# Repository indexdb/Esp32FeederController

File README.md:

# Esp32FeederController & RGB WS2812 Controller

The project is forked from
https://github.com/atanisoft/Esp32FeederController

I added two RGB WS2812 Lights Controller

`M810 L{1|2} R{0-255} G{0-255} B{0-255}` to turn on light

`M811 L{1|2}` to turn off light

The Esp32FeederController project allows controlling of multiple 0816 Feeders
using four wire cables.

## Supported Feeders

At this time the following feeder designs should work:

* [Original 0816 Feeder](https://docs.mgrl.de/maschine:pickandplace:feeder:0816feeder).
* [0816 Lumen Feeder](https://github.com/SupaCoder/0816-Lumen-SMT-Feeder-Remix).
* [Max Feeder](https://github.com/CurlyTaleGamesLLC/MAXFeederShield).

The [Max Feeder](https://github.com/CurlyTaleGamesLLC/MAXFeederShield) is the preferred
version of the feeder design as it supports adding a QR Code to the feeder that can be
used for automatic part identification.

### Feeder modifications / Addons

* [Reel holder](https://www.thingiverse.com/thing:3810696)
* [Vertical tape puller](https://github.com/SebG3D/TapePuller/wiki)

## Non-automatic feeders

* [Lumen Push/Pull Feeder](https://github.com/GatCode/LumenPPF)

# Adding Esp32FeederController to OpenPnP

Adding Esp32FeederController to OpenPnP consists of three steps:

* Create [GcodeDriver](https://github.com/openpnp/openpnp/wiki/GcodeDriver).
* Create [Actuators](https://github.com/openpnp/openpnp/wiki/Setup-and-Calibration%3A-Actuators) for Feeder actions.
* Create [Feeders](https://github.com/openpnp/openpnp/wiki/Setup-and-Calibration%3A-Feeders). 

### Creating the Gcode Driver

Each Esp32FeederController PCB should have it's own [GcodeDriver](https://github.com/openpnp/openpnp/wiki/GcodeDriver).

Steps to add a new [GcodeDriver](https://github.com/openpnp/openpnp/wiki/GcodeDriver) for Esp32FeederController:

* Navigate to the `Machine Setup` tab
* Traverse the list to the `Drivers` section, select and expand it.
* Click the `+` (add) icon and select `GcodeDriver`.
* Select the newly created `GcodeDriver GcodeDriver` entry.
* Set the `Name` so it can be easily identified later.
* Set `Communications Type` to `tcp`.
* Scroll down to the `TCP` section.
* Set `IP Address` based on the reported IP address in the serial output.
* Set `Port` to `8989`.
* Click the `Apply` button to save the updates.
* In the `File` menu select `Save Configuration` to ensure settings are not lost when restarting OpenPnP.

### Creating Actuators

Each Esp32FeederController PCB requires two `Actuators`:

* Feeder Advancement
* Feeder Post Pick

The following steps should be executed for the two `Actuators`:

* Navigate to the `Machine Setup` tab
* Traverse the list to the `Actuators` section, select and expand it.
* Click the `+` (add) icon and select `ReferenceActuator`.
* Select the newly created `ReferenceActuator ReferenceActuator` entry.
* Set `Driver` to the Esp32FeederController driver created previously.
* Set the `Name` so it can be easily identified later.
* Set `Value Type` to `Double`.
* Click the `Apply` button to save the updates.
* In the `File` menu select `Save Configuration` to ensure settings are not lost when restarting OpenPnP.

After the two `Actuators` have been defined it is necessary to configure the
Gcode commands to send for actuation, use the following steps to configure this:

* Navigate to the `Machine Setup` tab
* Traverse the list to the `Drivers` section, select and expand it.
* Click the `GcodeDriver Esp32FeederController` (or whatever name was provided previously).
* Navigate to the `Gcode` tab.
* In `Head Mountable` drop down select `Default`.
  * In `Setting` select `COMMAND_CONFIRM_REGEX` and enter `^ok.*`, be sure to click `Apply` before moving further.
  * In `Setting` select `COMMAND_ERROR_REGEX` and enter `^error.*`, be sure to click `Apply` before moving further.
* In `Head Mountable` drop down select `Actuator: [No Head] Feeder Advancement`.
  * In `Setting` select `ACTUATE_DOUBLE_COMMAND` and enter `M610 N{IntegerValue}*`, be sure to click `Apply` before moving further.
* In `Head Mountable` drop down select `Actuator: [No Head] Feeder Post Pick`.
  * In `Setting` select `ACTUATE_DOUBLE_COMMAND` and enter `M611 N{IntegerValue}*`, be sure to click `Apply` before moving further.
* In the `File` menu select `Save Configuration` to ensure settings are not lost when restarting OpenPnP.

## Configuring Feeders in OpenPnP

There are two types of feeders that will work well with Esp32FeederController:

* [ReferenceAutoFeeder](https://github.com/openpnp/openpnp/wiki/ReferenceAutoFeeder)
* [ReferenceSlotAutoFeeder](https://github.com/openpnp/openpnp/wiki/ReferenceSlotAutoFeeder)

Both operate similarly using the `Actuators` defined above.

* Navigate to the `Feeders` tab
* Click the `+` (add) icon and select `ReferenceAutoFeeder` or `ReferenceSlotAutoFeeder`.
* Select the newly created `ReferenceAutoFeeder ReferenceAutoFeeder` or `ReferenceSlotAutoFeeder ReferenceSlotAutoFeeder` entry.
* Double click on the newly created row in the `Name` column and rename it for easier identification.
* Set `Feed Actuator` to `Feeder Advancement` (or whichever name you provide the `Actuator`)
* Set `Post Pick Actuator` to `Feeder Post Pick` (or whichever name you provide the `Actuator`)
* Set `Actuator Value` on both `Actuators` to the feeder number on the Esp32FeederController PCB minus one (zero indexed).
* Click the `Apply` button to save the updates.
* In the `File` menu select `Save Configuration` to ensure settings are not lost when restarting OpenPnP.

Use the `Test Feed` and `Test post pick` to confirm the feeder is responding correctly.

## Supported Gcode commands

The Esp32FeederController supports multiple Gcode commands, many of which are
not directly used by OpenPnP. Many of the commands are intended to be used with
substitution of values within `{ }` marks, anything within `[ ]` are optional
arguments.

### Feeder Movement (M610)

`M610 N{feeder} [D{distance}]`

* `{feeder}` is the Feeder to be moved forward.
* `{distance}` is the distance to move the feeder and is optional.

### Feeder Post Pick (M611)

`M611 N{feeder}`

* `{feeder}` is the Feeder to be moved as part of post-pick.

### Feeder Status (M612)

`M612 N{feeder}`

* `{feeder}` is the Feeder to retrieve status for.

### Feeder Configuration (M613)

`M613 N{feeder} [A{advance angle}] [B{half advance angle}] [C{retract angle}] [D{degrees}] [F{feed length}] [S{speed}] [U{settle time}] [V{min pulse}] [W{max pulse}] [Z{feedback enabled}]`

All parameters except `{feeder}` are optional.

* `{feeder}` is the Feeder to be configured.
* `{advance angle}` is the angle to move the servo to for full extension.
* `{half advance angle}` is the angle to move the servo to for half extension.
* `{retract angle}` is the angle to move the servo to for retraction.
* `{degrees}` is the maximum number of degrees to move at one time, set to zero to move immediately.
* `{feed length}` is the number of millimeters (pitch) to move the feeder forward when moving to the next part and must be a multiple of 2.
* `{speed}` is the interval at which to move the servo between two angles, used in conjunction with `{degrees}`.
* `{settle time}` is the number of milliseconds to delay between servo movements.
* `{min pulse}` is the minimum number of pulses to send the servo.
* `{max pulse}` is the maximum number of pulses to send the servo.
* `{feedback enabled}` is used to enable or disable feedback checking as part of movement, set to zero to disable or one to enable

### Enable Feeder (M614)

`M614 N{feeder}`

* `{feeder}` is the Feeder to enable.

### Disable Feeder (M615)

`M615 N{feeder}`

* `{feeder}` is the Feeder to disable.

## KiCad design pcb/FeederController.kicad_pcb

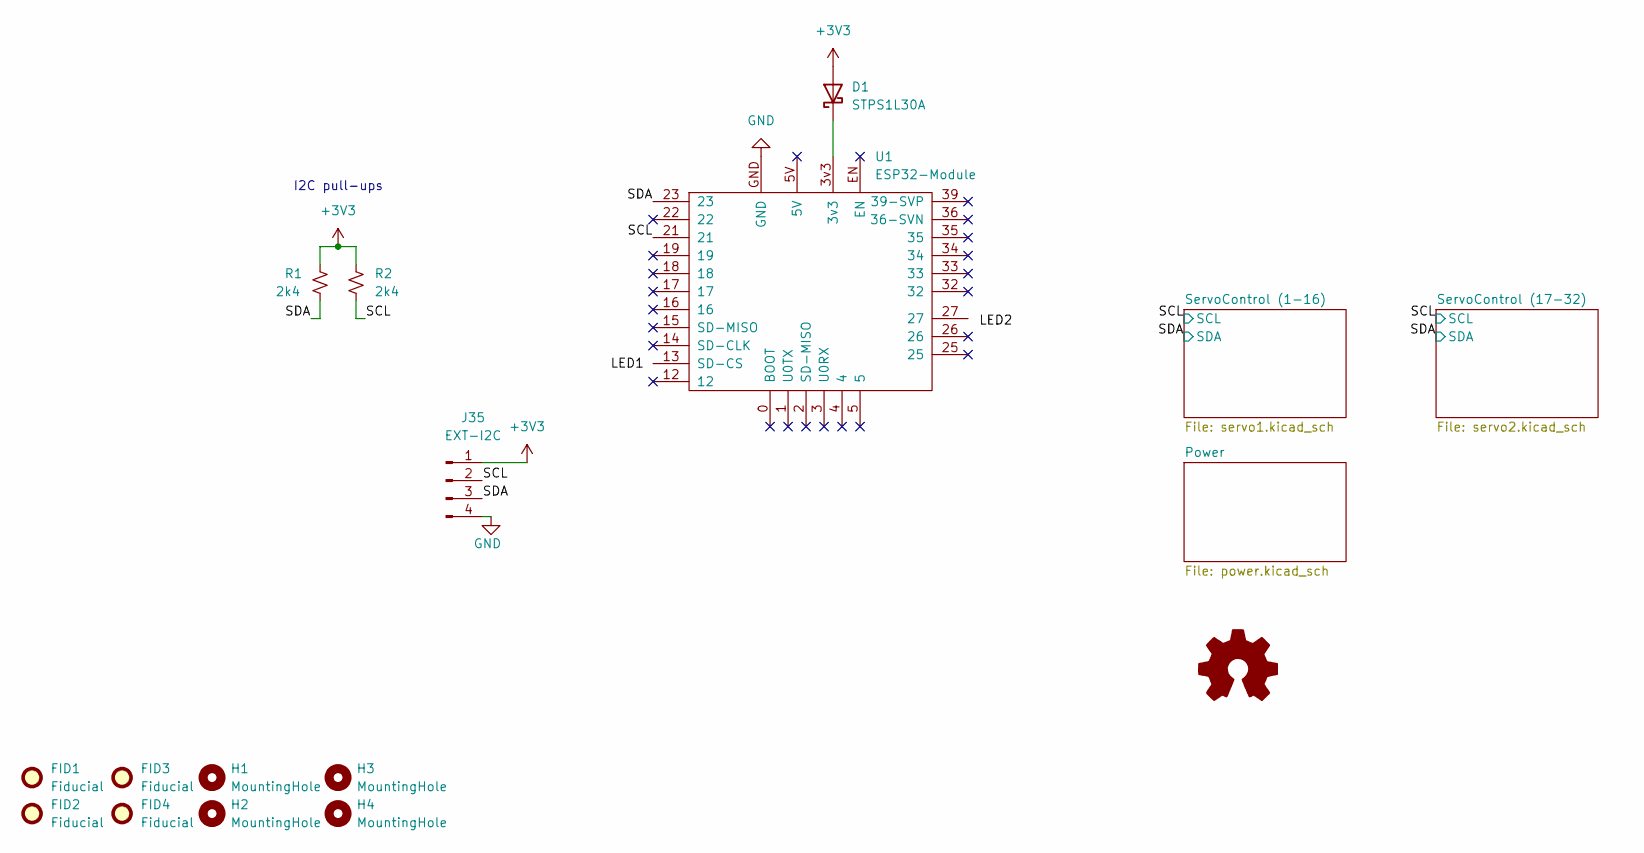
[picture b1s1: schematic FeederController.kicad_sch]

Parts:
D1: STPS1L30A; D_SMA_Handsoldering; Mouser 511-STPS1L30AFN
FID1, FID2, FID3, FID4: Fiducial; Fiducial_0.5mm_Mask1mm
H1, H2, H3, H4: MountingHole; MountingHole_3.2mm_M3_Pad
J35: EXT-I2C; PinHeader_1x04_P2.54mm_Vertical
R1, R2: 2k4; R_0603_1608Metric_Pad0.98x0.95mm_HandSolder
U1: ESP32-Module; TTGO-T1-DEVKIT-C

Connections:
/SCL: J35.2, R2.2, U1.21; also elsewhere on the board
/SDA: J35.3, R1.2, U1.23; also elsewhere on the board
GND: J35.4, U1.GND; also elsewhere on the board
unnamed: D1.1 (K), U1.3v3

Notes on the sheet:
I2C pull-ups

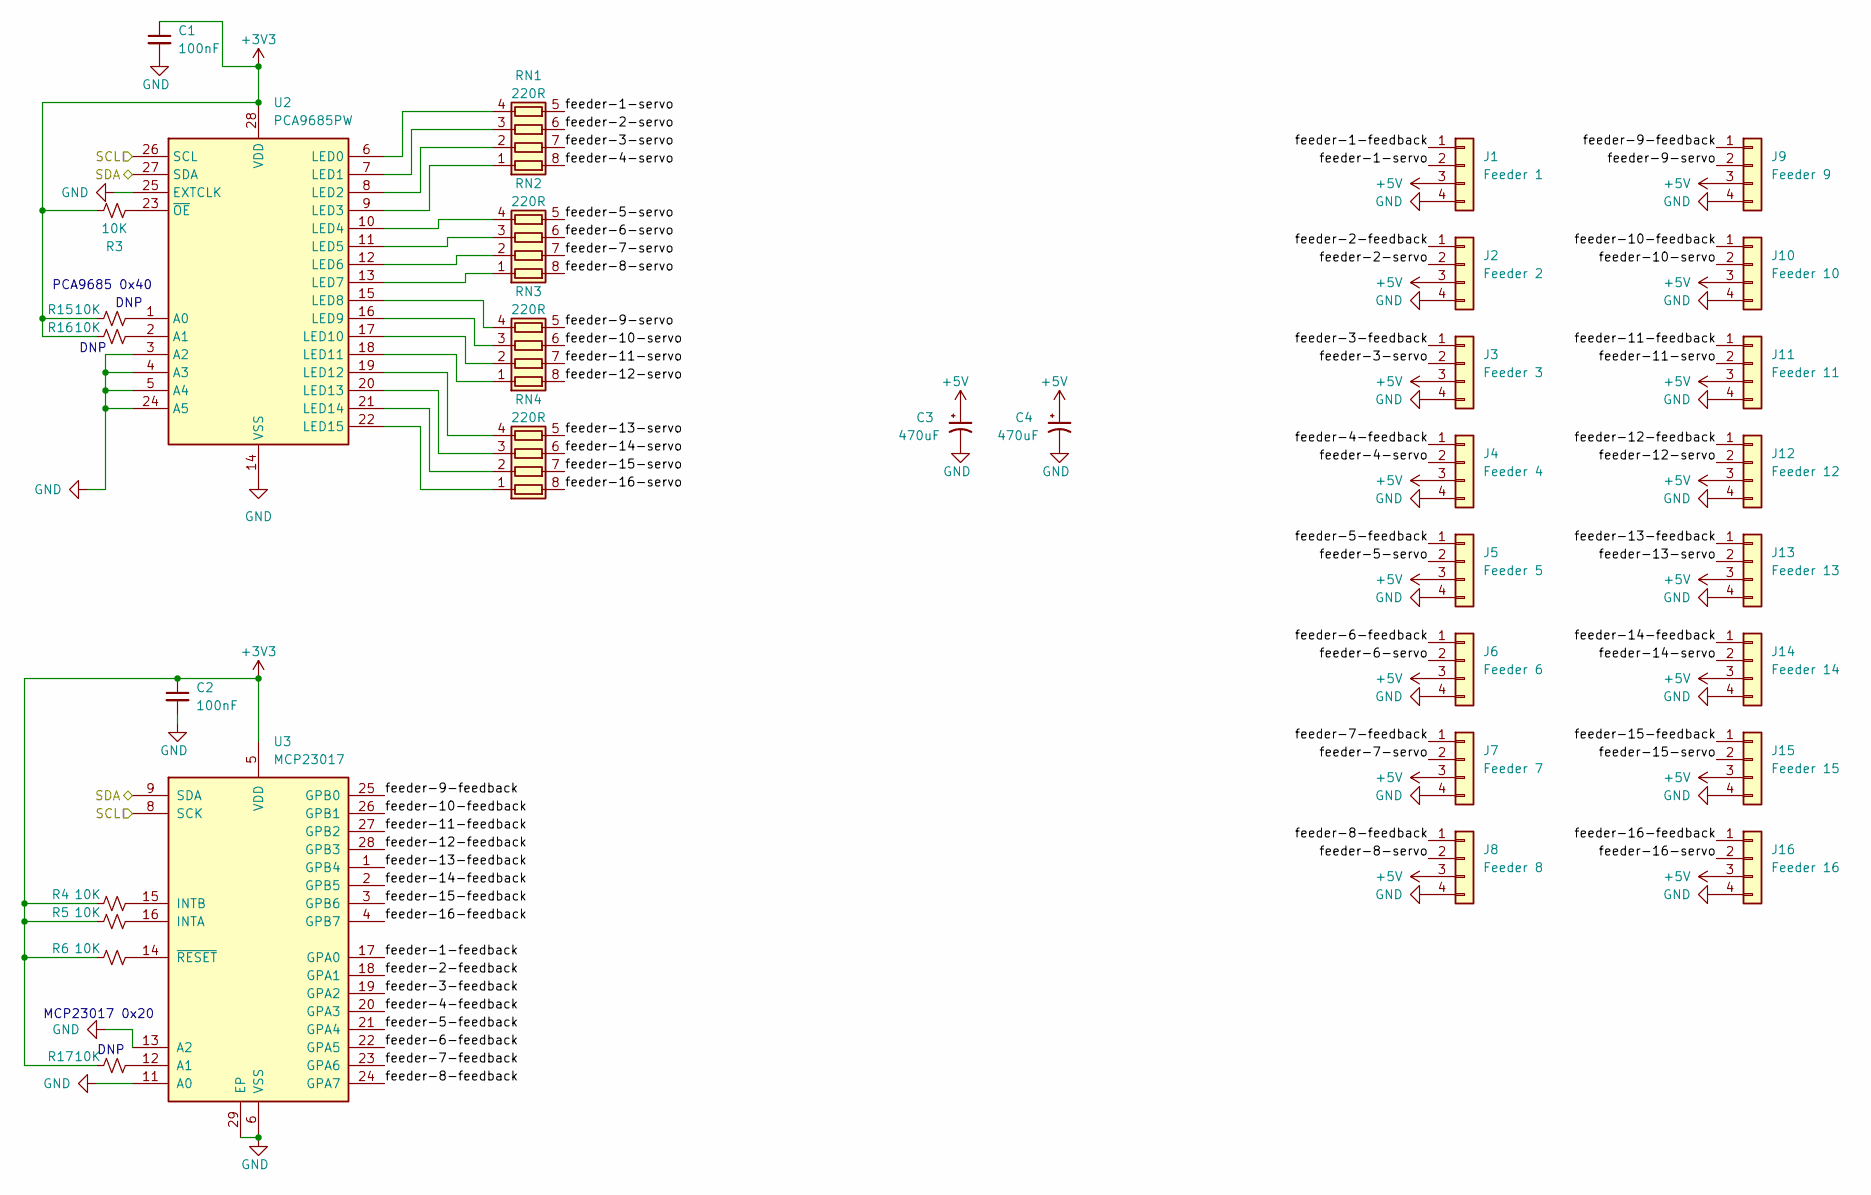
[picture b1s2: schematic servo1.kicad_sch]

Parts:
C1, C2: 100nF; C_0603_1608Metric_Pad1.08x0.95mm_HandSolder; Mouser 791-0603B822K250CT
C3, C4: 470uF; CP_Radial_D8.0mm_P5.00mm
J1: Feeder 1; PinHeader_1x04_P2.54mm_Vertical
J2: Feeder 2; PinHeader_1x04_P2.54mm_Vertical
J3: Feeder 3; PinHeader_1x04_P2.54mm_Vertical
J4: Feeder 4; PinHeader_1x04_P2.54mm_Vertical
J5: Feeder 5; PinHeader_1x04_P2.54mm_Vertical
J6: Feeder 6; PinHeader_1x04_P2.54mm_Vertical
J7: Feeder 7; PinHeader_1x04_P2.54mm_Vertical
J8: Feeder 8; PinHeader_1x04_P2.54mm_Vertical
J9: Feeder 9; PinHeader_1x04_P2.54mm_Vertical
J10: Feeder 10; PinHeader_1x04_P2.54mm_Vertical
J11: Feeder 11; PinHeader_1x04_P2.54mm_Vertical
J12: Feeder 12; PinHeader_1x04_P2.54mm_Vertical
J13: Feeder 13; PinHeader_1x04_P2.54mm_Vertical
J14: Feeder 14; PinHeader_1x04_P2.54mm_Vertical
J15: Feeder 15; PinHeader_1x04_P2.54mm_Vertical
J16: Feeder 16; PinHeader_1x04_P2.54mm_Vertical
R3, R4, R5, R6, R15, R16, R17: 10K; R_0603_1608Metric_Pad0.98x0.95mm_HandSolder; Mouser 279-CRGCQ0603F10K
RN1, RN2, RN3, RN4: 220R; R_Array_Concave_4x0402
U2: PCA9685PW; TSSOP-28_4.4x9.7mm_P0.65mm
U3: MCP23017; QFN-28-1EP_6x6mm_P0.65mm_EP4.25x4.25mm

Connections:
+5V: C3.1, C4.1, J1.3, J2.3, J3.3, J4.3, J5.3, J6.3, J7.3, J8.3, J9.3, J10.3, J11.3, J12.3, J13.3, J14.3, J15.3, J16.3; also elsewhere on the board
/SCL: U2.26 (SCL), U3.8 (SCK); also elsewhere on the board
/SDA: U2.27 (SDA), U3.9 (SDA); also elsewhere on the board
/ServoControl (1-16)/feeder-1-feedback: J1.1, U3.17 (GPA0)
/ServoControl (1-16)/feeder-1-servo: J1.2, RN1.5 (R4.2)
/ServoControl (1-16)/feeder-2-feedback: J2.1, U3.18 (GPA1)
/ServoControl (1-16)/feeder-2-servo: J2.2, RN1.6 (R3.2)
/ServoControl (1-16)/feeder-3-feedback: J3.1, U3.19 (GPA2)
/ServoControl (1-16)/feeder-3-servo: J3.2, RN1.7 (R2.2)
/ServoControl (1-16)/feeder-4-feedback: J4.1, U3.20 (GPA3)
/ServoControl (1-16)/feeder-4-servo: J4.2, RN1.8 (R1.2)
/ServoControl (1-16)/feeder-5-feedback: J5.1, U3.21 (GPA4)
/ServoControl (1-16)/feeder-5-servo: J5.2, RN2.5 (R4.2)
/ServoControl (1-16)/feeder-6-feedback: J6.1, U3.22 (GPA5)
/ServoControl (1-16)/feeder-6-servo: J6.2, RN2.6 (R3.2)
/ServoControl (1-16)/feeder-7-feedback: J7.1, U3.23 (GPA6)
/ServoControl (1-16)/feeder-7-servo: J7.2, RN2.7 (R2.2)
/ServoControl (1-16)/feeder-8-feedback: J8.1, U3.24 (GPA7)
/ServoControl (1-16)/feeder-8-servo: J8.2, RN2.8 (R1.2)
/ServoControl (1-16)/feeder-9-feedback: J9.1, U3.25 (GPB0)
/ServoControl (1-16)/feeder-9-servo: J9.2, RN3.5 (R4.2)
/ServoControl (1-16)/feeder-10-feedback: J10.1, U3.26 (GPB1)
/ServoControl (1-16)/feeder-10-servo: J10.2, RN3.6 (R3.2)
/ServoControl (1-16)/feeder-11-feedback: J11.1, U3.27 (GPB2)
/ServoControl (1-16)/feeder-11-servo: J11.2, RN3.7 (R2.2)
/ServoControl (1-16)/feeder-12-feedback: J12.1, U3.28 (GPB3)
/ServoControl (1-16)/feeder-12-servo: J12.2, RN3.8 (R1.2)
/ServoControl (1-16)/feeder-13-feedback: J13.1, U3.1 (GPB4)
/ServoControl (1-16)/feeder-13-servo: J13.2, RN4.5 (R4.2)
/ServoControl (1-16)/feeder-14-feedback: J14.1, U3.2 (GPB5)
/ServoControl (1-16)/feeder-14-servo: J14.2, RN4.6 (R3.2)
/ServoControl (1-16)/feeder-15-feedback: J15.1, U3.3 (GPB6)
/ServoControl (1-16)/feeder-15-servo: J15.2, RN4.7 (R2.2)
/ServoControl (1-16)/feeder-16-feedback: J16.1, U3.4 (GPB7)
/ServoControl (1-16)/feeder-16-servo: J16.2, RN4.8 (R1.2)
GND: C1.2, C2.2, C3.2, C4.2, J1.4, J2.4, J3.4, J4.4, J5.4, J6.4, J7.4, J8.4, J9.4, J10.4, J11.4, J12.4, J13.4, J14.4, J15.4, J16.4, R3.2, U2.3 (A2), U2.4 (A3), U2.5 (A4), U2.14 (VSS), U2.23 (~OE), U2.24 (A5), U2.25 (EXTCLK), U3.6 (VSS), U3.11 (A0), U3.13 (A2), U3.29 (EP); also elsewhere on the board
unnamed: R4.2, U3.15 (INTB)
unnamed: R5.2, U3.16 (INTA)
unnamed: R6.2, U3.14 (~RESET)
unnamed: RN1.1 (R1.1), U2.9 (LED3)
unnamed: RN1.2 (R2.1), U2.8 (LED2)
unnamed: RN1.3 (R3.1), U2.7 (LED1)
unnamed: RN1.4 (R4.1), U2.6 (LED0)
unnamed: RN2.1 (R1.1), U2.13 (LED7)
unnamed: RN2.2 (R2.1), U2.12 (LED6)
unnamed: RN2.3 (R3.1), U2.11 (LED5)
unnamed: RN2.4 (R4.1), U2.10 (LED4)
unnamed: RN3.1 (R1.1), U2.18 (LED11)
unnamed: RN3.2 (R2.1), U2.17 (LED10)
unnamed: RN3.3 (R3.1), U2.16 (LED9)
unnamed: RN3.4 (R4.1), U2.15 (LED8)
unnamed: RN4.1 (R1.1), U2.22 (LED15)
unnamed: RN4.2 (R2.1), U2.21 (LED14)
unnamed: RN4.3 (R3.1), U2.20 (LED13)
unnamed: RN4.4 (R4.1), U2.19 (LED12)
unnamed: R15.2, U2.1 (A0)
unnamed: R16.2, U2.2 (A1)
unnamed: R17.2, U3.12 (A1)

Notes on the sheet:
MCP23017 0x20
PCA9685 0x40
DNP

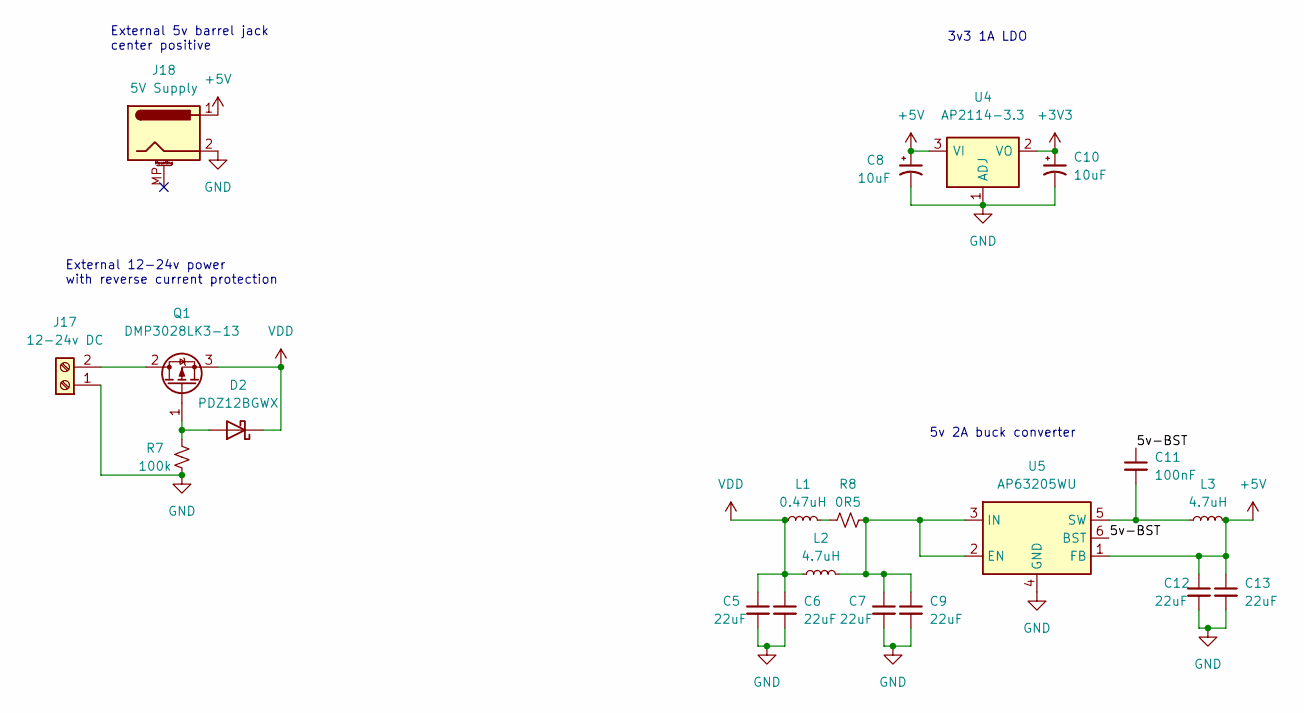
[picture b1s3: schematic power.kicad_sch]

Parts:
C5, C6, C9, C12, C13: 22uF; C_0603_1608Metric_Pad1.08x0.95mm_HandSolder; Mouser 810-C1608X5R0J226M
C7: 22uF; C_0603_1608Metric_Pad1.08x0.95mm_HandSolder; Mouser 810-C1608X5R0J226
C8, C10: 10uF; CP_Elec_5x5.3; Mouser 710-865230542002
C11: 100nF; C_0603_1608Metric_Pad1.08x0.95mm_HandSolder; Mouser 603-CC603KPX7R9BB104
D2: PDZ12BGWX; D_SOD-123; Mouser 771-PDZ12BGWX
J17: 12-24v DC; TerminalBlock_Phoenix_MKDS-1,5-2-5.08_1x02_P5.08mm_Horizont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; Mouser 649-220316-H021B01LF
J18: 5V Supply; BarrelJack_Horizontal
L1: 0.47uH; L_0603_1608Metric_Pad1.05x0.95mm_HandSolder; Mouser 810-MLZ1608DR47DT000
L2, L3: 4.7uH; L_Taiyo-Yuden_NR-40xx_HandSoldering; Mouser 963-NRS4018T4R7MDGJ
Q1: DMP3028LK3-13; TO-252-2; Mouser 621-DMP3028LK3-13
R7: 100k; R_1206_3216Metric_Pad1.30x1.75mm_HandSolder; Mouser 71-CRCW1206100KFKEAC
R8: 0R5; R_0805_2012Metric_Pad1.20x1.40mm_HandSolder; Mouser 756-LRCS0805-R50FT5
U4: AP2114-3.3; SOT-223-3_TabPin2; Mouser 621-AP2114H-3.3TRG1
U5: AP63205WU; TSOT-23-6; Mouser 621-AP63205WU-7

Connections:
+5V: C8.1, C12.1, C13.1, J18.1, L3.2, U4.3 (VI), U5.1 (FB); also elsewhere on the board
/Power/5v-BST: C11.1, U5.6 (BST)
GND: C5.2, C6.2, C7.2, C8.2, C9.2, C10.2, C12.2, C13.2, J17.1, J18.2, R7.1, U4.1 (ADJ), U5.4 (GND); also elsewhere on the board
unnamed: C7.1, C9.1, L2.2, R8.2, U5.2 (EN), U5.3 (IN)
unnamed: C11.2, L3.1, U5.5 (SW)
unnamed: D2.2 (A), Q1.1 (G), R7.2
unnamed: J17.2, Q1.2 (D)
unnamed: L1.2, R8.1
VDD: C5.1, C6.1, D2.1 (K), L1.1, L2.1, Q1.3 (S)

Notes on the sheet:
5v 2A buck converter
External 12-24v power with reverse current protection
3v3 1A LDO
External 5v barrel jack center positive

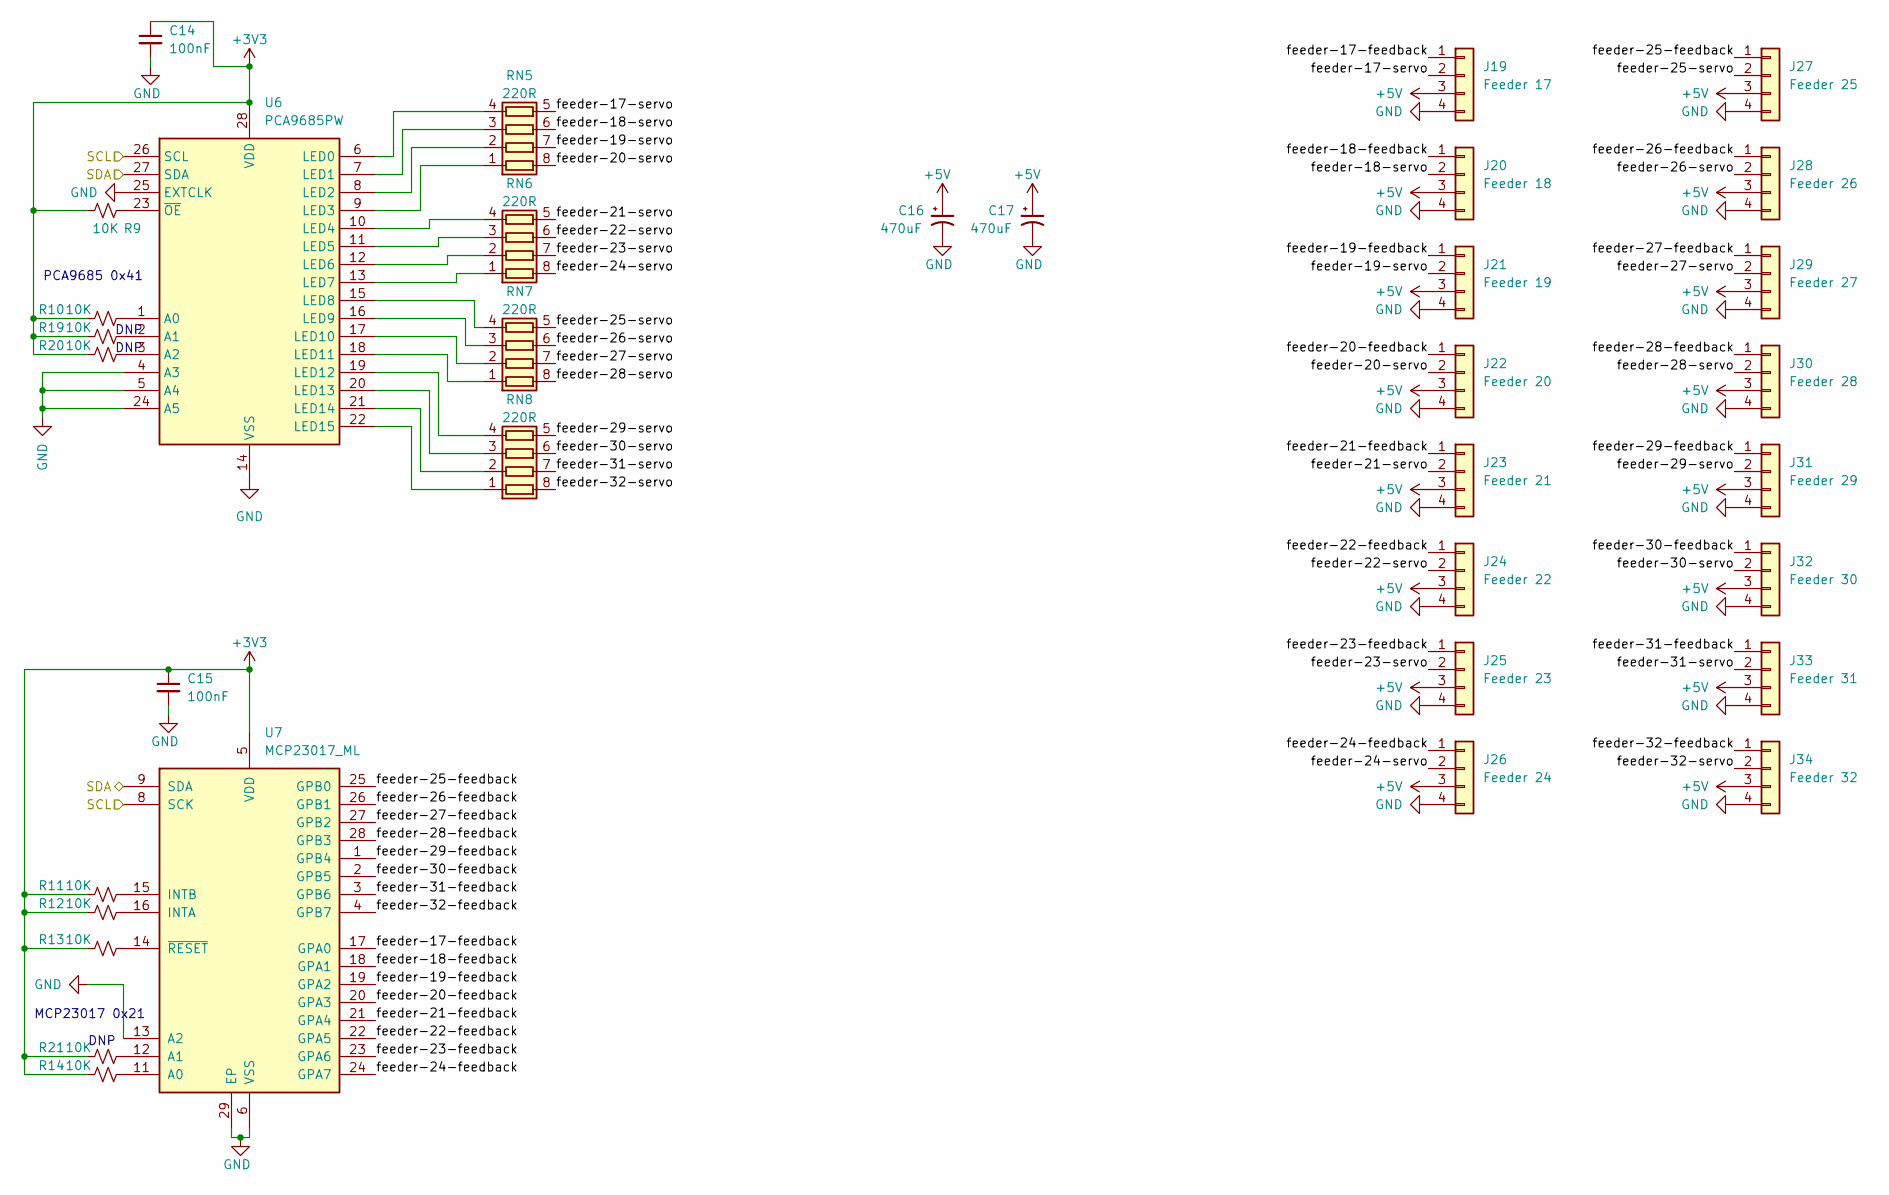
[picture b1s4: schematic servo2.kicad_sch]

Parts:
C14: 100nF; C_0603_1608Metric_Pad1.08x0.95mm_HandSolder
C15: 100nF; C_0603_1608Metric_Pad1.08x0.95mm_HandSolder; Mouser 791-0603B822K250CT
C16, C17: 470uF; CP_Radial_D8.0mm_P5.00mm
J19: Feeder 17; PinHeader_1x04_P2.54mm_Vertical
J20: Feeder 18; PinHeader_1x04_P2.54mm_Vertical
J21: Feeder 19; PinHeader_1x04_P2.54mm_Vertical
J22: Feeder 20; PinHeader_1x04_P2.54mm_Vertical
J23: Feeder 21; PinHeader_1x04_P2.54mm_Vertical
J24: Feeder 22; PinHeader_1x04_P2.54mm_Vertical
J25: Feeder 23; PinHeader_1x04_P2.54mm_Vertical
J26: Feeder 24; PinHeader_1x04_P2.54mm_Vertical
J27: Feeder 25; PinHeader_1x04_P2.54mm_Vertical
J28: Feeder 26; PinHeader_1x04_P2.54mm_Vertical
J29: Feeder 27; PinHeader_1x04_P2.54mm_Vertical
J30: Feeder 28; PinHeader_1x04_P2.54mm_Vertical
J31: Feeder 29; PinHeader_1x04_P2.54mm_Vertical
J32: Feeder 30; PinHeader_1x04_P2.54mm_Vertical
J33: Feeder 31; PinHeader_1x04_P2.54mm_Vertical
J34: Feeder 32; PinHeader_1x04_P2.54mm_Vertical
R9, R10, R11, R12, R13, R14, R19, R20, R21: 10K; R_0603_1608Metric_Pad0.98x0.95mm_HandSolder; Mouser 279-CRGCQ0603F10K
RN5, RN6, RN7, RN8: 220R; R_Array_Concave_4x0402
U6: PCA9685PW; TSSOP-28_4.4x9.7mm_P0.65mm
U7: MCP23017_ML; QFN-28-1EP_6x6mm_P0.65mm_EP4.25x4.25mm

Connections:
+5V: C16.1, C17.1, J19.3, J20.3, J21.3, J22.3, J23.3, J24.3, J25.3, J26.3, J27.3, J28.3, J29.3, J30.3, J31.3, J32.3, J33.3, J34.3; also elsewhere on the board
/SCL: U6.26 (SCL), U7.8 (SCK); also elsewhere on the board
/SDA: U6.27 (SDA), U7.9 (SDA); also elsewhere on the board
/ServoControl (17-32)/feeder-17-servo: J19.2, RN5.5 (R4.2); also elsewhere on the board
/ServoControl (17-32)/feeder-18-feedback: J20.1, U7.18 (GPA1)
/ServoControl (17-32)/feeder-18-servo: J20.2, RN5.6 (R3.2)
/ServoControl (17-32)/feeder-19-feedback: J21.1, U7.19 (GPA2)
/ServoControl (17-32)/feeder-19-servo: J21.2, RN5.7 (R2.2)
/ServoControl (17-32)/feeder-20-feedback: J22.1, U7.20 (GPA3)
/ServoControl (17-32)/feeder-20-servo: J22.2, RN5.8 (R1.2)
/ServoControl (17-32)/feeder-21-feedback: J23.1, U7.21 (GPA4)
/ServoControl (17-32)/feeder-21-servo: J23.2, RN6.5 (R4.2)
/ServoControl (17-32)/feeder-22-feedback: J24.1, U7.22 (GPA5)
/ServoControl (17-32)/feeder-22-servo: J24.2, RN6.6 (R3.2)
/ServoControl (17-32)/feeder-23-feedback: J25.1, U7.23 (GPA6)
/ServoControl (17-32)/feeder-23-servo: J25.2, RN6.7 (R2.2)
/ServoControl (17-32)/feeder-24-feedback: J26.1, U7.24 (GPA7)
/ServoControl (17-32)/feeder-24-servo: J26.2, RN6.8 (R1.2)
/ServoControl (17-32)/feeder-25-feedback: J27.1, U7.25 (GPB0)
/ServoControl (17-32)/feeder-25-servo: J27.2, RN7.5 (R4.2)
/ServoControl (17-32)/feeder-26-feedback: J28.1, U7.26 (GPB1)
/ServoControl (17-32)/feeder-26-servo: J28.2, RN7.6 (R3.2)
/ServoControl (17-32)/feeder-27-feedback: J29.1, U7.27 (GPB2)
/ServoControl (17-32)/feeder-27-servo: J29.2, RN7.7 (R2.2)
/ServoControl (17-32)/feeder-28-feedback: J30.1, U7.28 (GPB3)
/ServoControl (17-32)/feeder-28-servo: J30.2, RN7.8 (R1.2)
/ServoControl (17-32)/feeder-29-feedback: J31.1, U7.1 (GPB4)
/ServoControl (17-32)/feeder-29-servo: J31.2, RN8.5 (R4.2)
/ServoControl (17-32)/feeder-30-feedback: J32.1, U7.2 (GPB5)
/ServoControl (17-32)/feeder-30-servo: J32.2, RN8.6 (R3.2)
/ServoControl (17-32)/feeder-31-feedback: J33.1, U7.3 (GPB6)
/ServoControl (17-32)/feeder-31-servo: J33.2, RN8.7 (R2.2)
/ServoControl (17-32)/feeder-32-feedback: J34.1, U7.4 (GPB7)
/ServoControl (17-32)/feeder-32-servo: J34.2, RN8.8 (R1.2)
GND: C14.2, C15.2, C16.2, C17.2, J19.4, J20.4, J21.4, J22.4, J23.4, J24.4, J25.4, J26.4, J27.4, J28.4, J29.4, J30.4, J31.4, J32.4, J33.4, J34.4, R9.2, U6.4 (A3), U6.5 (A4), U6.14 (VSS), U6.23 (~OE), U6.24 (A5), U6.25 (EXTCLK), U7.6 (VSS), U7.13 (A2), U7.29 (EP); also elsewhere on the board
unnamed: R10.2, U6.1 (A0)
unnamed: R11.2, U7.15 (INTB)
unnamed: R12.2, U7.16 (INTA)
unnamed: R13.2, U7.14 (~RESET)
unnamed: R14.2, U7.11 (A0)
unnamed: RN5.1 (R1.1), U6.9 (LED3)
unnamed: RN5.2 (R2.1), U6.8 (LED2)
unnamed: RN5.3 (R3.1), U6.7 (LED1)
unnamed: RN5.4 (R4.1), U6.6 (LED0)
unnamed: RN6.1 (R1.1), U6.13 (LED7)
unnamed: RN6.2 (R2.1), U6.12 (LED6)
unnamed: RN6.3 (R3.1), U6.11 (LED5)
unnamed: RN6.4 (R4.1), U6.10 (LED4)
unnamed: RN7.1 (R1.1), U6.18 (LED11)
unnamed: RN7.2 (R2.1), U6.17 (LED10)
unnamed: RN7.3 (R3.1), U6.16 (LED9)
unnamed: RN7.4 (R4.1), U6.15 (LED8)
unnamed: RN8.1 (R1.1), U6.22 (LED15)
unnamed: RN8.2 (R2.1), U6.21 (LED14)
unnamed: RN8.3 (R3.1), U6.20 (LED13)
unnamed: RN8.4 (R4.1), U6.19 (LED12)
unnamed: R19.2, U6.2 (A1)
unnamed: R20.2, U6.3 (A2)
unnamed: R21.2, U7.12 (A1)

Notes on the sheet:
DNP
MCP23017 0x21
PCA9685 0x41

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
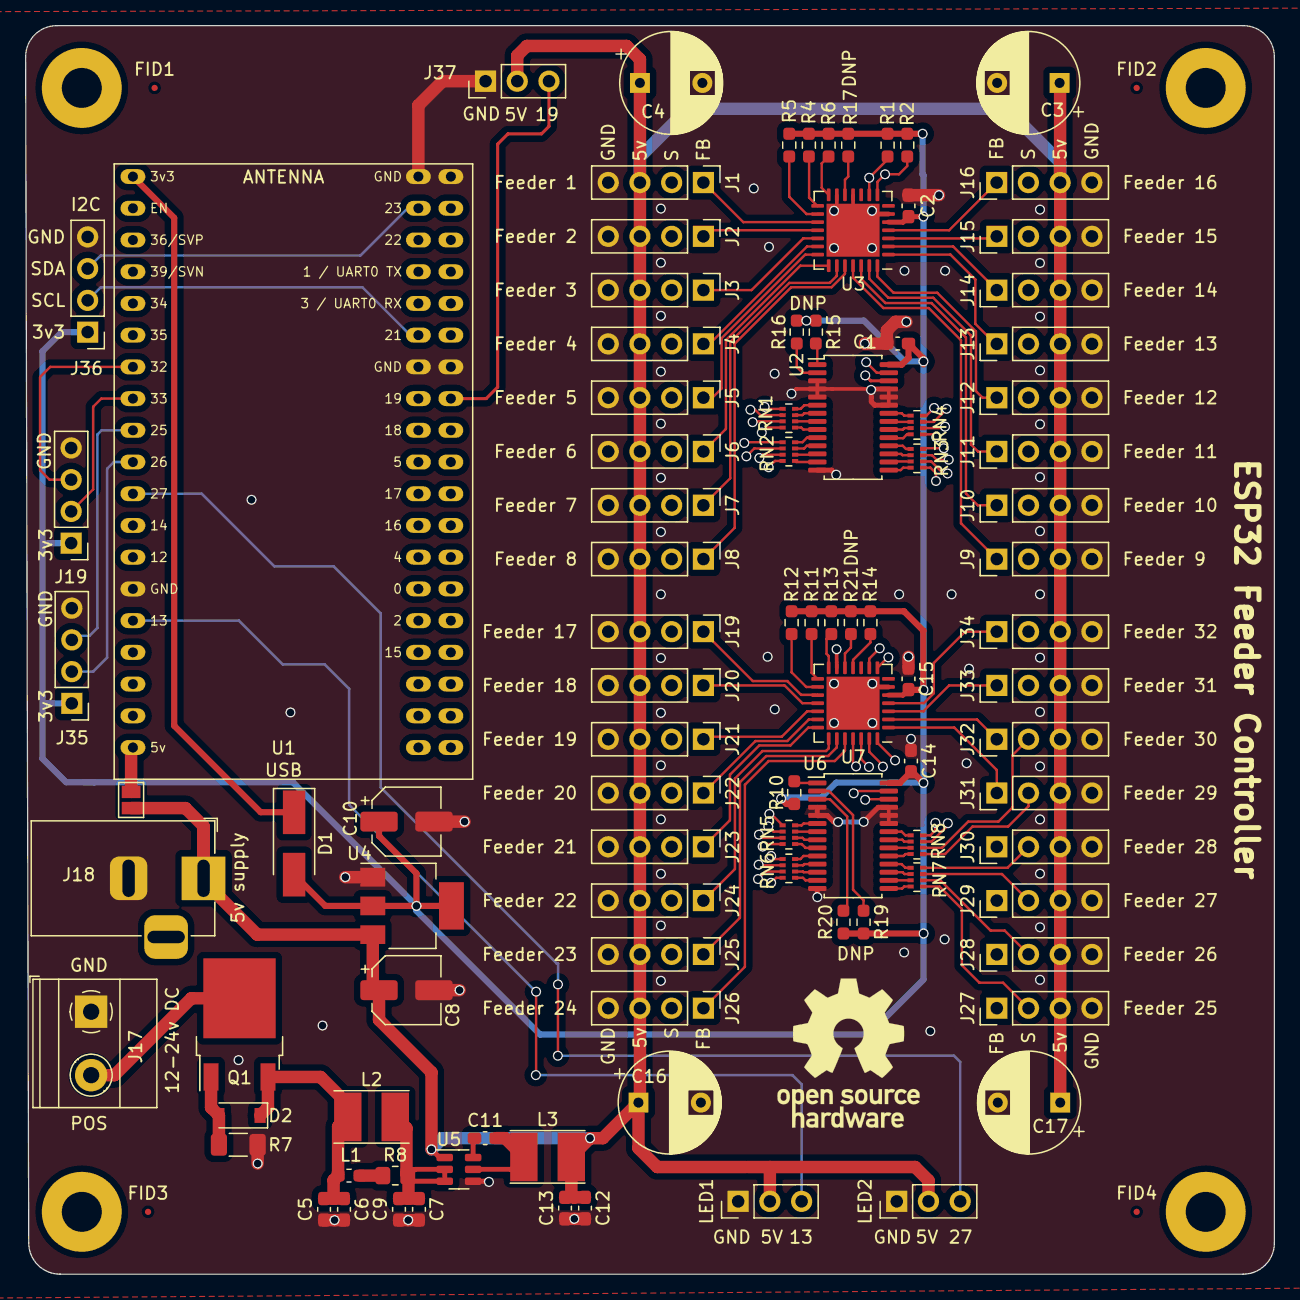
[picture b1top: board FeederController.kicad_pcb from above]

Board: 4 copper layers, 100.0 x 100.0 mm, 104 parts (0 on the bottom side), 123 nets.

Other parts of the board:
J19#2: Feeder 17; PinHeader_1x04_P2.54mm_Vertical
J36: EXT-I2C; PinHeader_1x04_P2.54mm_Vertical
LED1, LED1#2, LED2: PinHeader_1x03_P2.54mm_Vertical

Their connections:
+5V: J19#2.3, LED1.2, LED1#2.2, LED2.2; also elsewhere on the board
/SCL: J36.2; also elsewhere on the board
/SDA: J36.3; also elsewhere on the board
/ServoControl (17-32)/feeder-17-servo: J19#2.2; also elsewhere on the board
GND: J19#2.4, J36.4, LED1.1, LED1#2.1, LED2.1; also elsewhere on the board

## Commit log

2023-04-01 Changes to be committed: new file: main/RGBLed.hxx
2023-04-02 Changes to be committed: modified: main/CMakeLists.txt modified: main/Utils.hxx modified: main/WiFiManager.cpp modified: main/WiFiManager.hxx modified: main/config.hxx modified: main/idf_component.ym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
2023-04-02 Changes to be committed: modified: README.md
2023-04-05 Changes to be committed: modified: main/RGBLed.hxx modified: main/config.hxx
2023-04-05 Changes to be committed: modified: main/RGBLed.hxx
2023-04-16 Changes to be committed: modified: ../pcb/FeederController.kicad_pcb modified: ../pcb/FeederController.kicad_prl modified: ../pcb/FeederController.kicad_pro modified: ../pcb/FeederController.kicad_sc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
    Untracked files:
    ../pcb/FeederController.csv
    ../pcb/FeederController.xml
